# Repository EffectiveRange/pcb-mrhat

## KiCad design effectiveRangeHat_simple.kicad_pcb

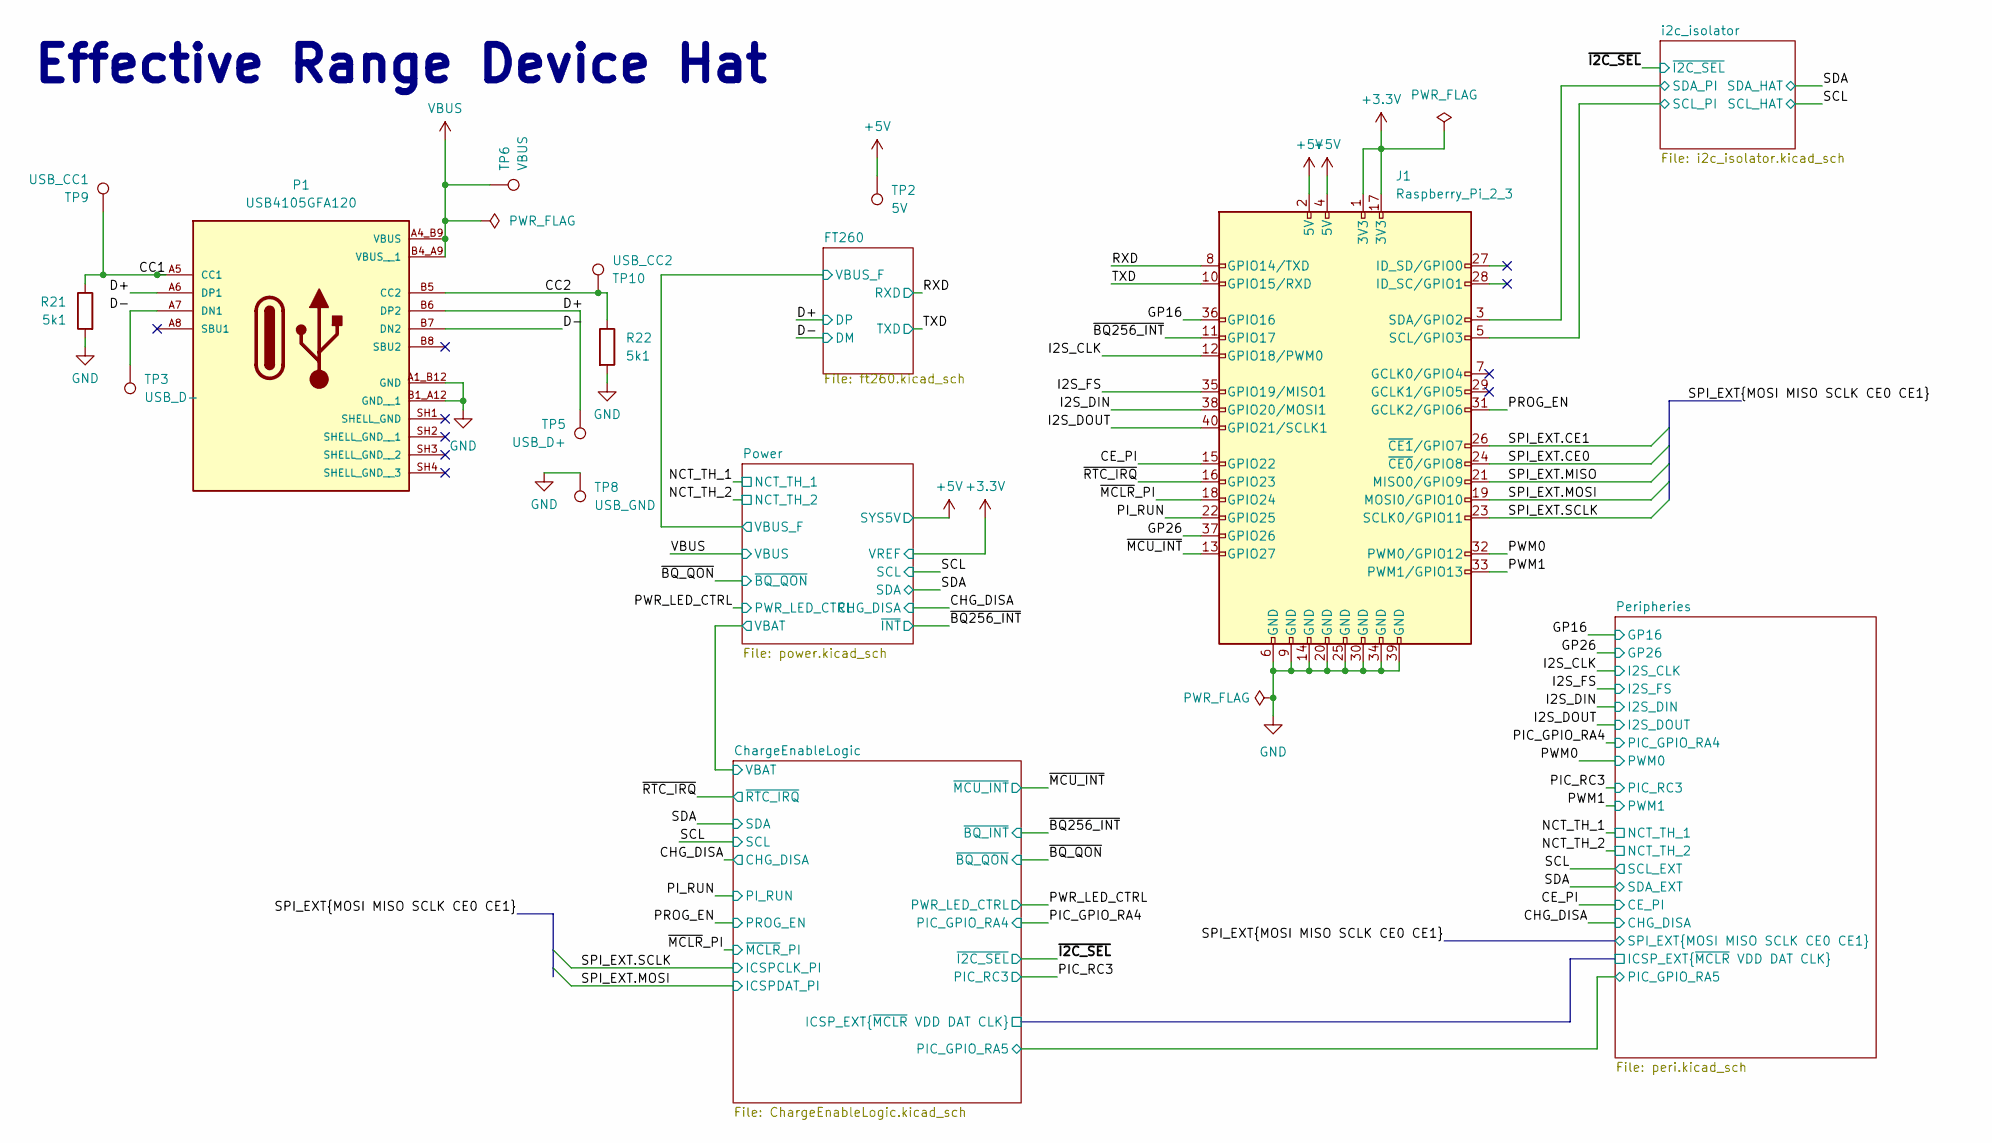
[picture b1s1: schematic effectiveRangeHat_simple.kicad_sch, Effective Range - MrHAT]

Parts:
J1: Raspberry_Pi_2_3; Raspberry_Pi_Zero_MountingHoles; MPN 61304021121
P1: USB4105GFA120; GCT_USB4105GFA120; PARTREV B3
R21, R22: 5k1; R_0402_1005Metric; MPN ERA-2AEB512X
TP2: 5V; TestPoint_Pad_D1.0mm
TP3: USB_D-; TestPoint_Pad_D1.0mm
TP5: USB_D+; TestPoint_Pad_D1.0mm
TP6: VBUS; TestPoint_Pad_D1.0mm
TP8: USB_GND; TestPoint_Pad_D1.0mm
TP9: USB_CC1; TestPoint_Pad_D1.0mm
TP10: USB_CC2; TestPoint_Pad_D1.0mm

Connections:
+3.3V: J1.1 (3V3), J1.17 (3V3); also elsewhere on the board
+5V: J1.2 (5V), J1.4 (5V), TP2.1; also elsewhere on the board
/CC1: P1.A5 (CC1), R21.1, TP9.1
/CC2: P1.B5 (CC2), R22.1, TP10.1
/CE_PI: J1.15 (GPIO22); also elsewhere on the board
/D+: P1.A6 (DP1), P1.B6 (DP2), TP5.1; also elsewhere on the board
/D-: P1.A7 (DN1), P1.B7 (DN2), TP3.1; also elsewhere on the board
/GP16: J1.36 (GPIO16); also elsewhere on the board
/GP26: J1.37 (GPIO26); also elsewhere on the board
/I2S_CLK: J1.12 (GPIO18/PWM0); also elsewhere on the board
/I2S_DIN: J1.38 (GPIO20/MOSI1); also elsewhere on the board
/I2S_DOUT: J1.40 (GPIO21/SCLK1); also elsewhere on the board
/I2S_FS: J1.35 (GPIO19/MISO1); also elsewhere on the board
/PI_RUN: J1.22 (GPIO25); also elsewhere on the board
/PROG_EN: J1.31 (GCLK2/GPIO6); also elsewhere on the board
/PWM0: J1.32 (PWM0/GPIO12); also elsewhere on the board
/PWM1: J1.33 (PWM1/GPIO13); also elsewhere on the board
/RXD: J1.8 (GPIO14/TXD); also elsewhere on the board
/SPI_EXT.CE0: J1.24 (~CE0/GPIO8); also elsewhere on the board
/SPI_EXT.CE1: J1.26 (~CE1/GPIO7); also elsewhere on the board
/SPI_EXT.MISO: J1.21 (MISO0/GPIO9); also elsewhere on the board
/SPI_EXT.MOSI: J1.19 (MOSI0/GPIO10); also elsewhere on the board
/SPI_EXT.SCLK: J1.23 (SCLK0/GPIO11); also elsewhere on the board
/TXD: J1.10 (GPIO15/RXD); also elsewhere on the board
/i2c_isolator/SCL_PI: J1.5 (SCL/GPIO3); also elsewhere on the board
/i2c_isolator/SDA_PI: J1.3 (SDA/GPIO2); also elsewhere on the board
/~BQ256_INT: J1.11 (GPIO17); also elsewhere on the board
/~MCLR_PI: J1.18 (GPIO24); also elsewhere on the board
/~MCU_INT: J1.13 (GPIO27); also elsewhere on the board
/~RTC_IRQ: J1.16 (GPIO23); also elsewhere on the board
GND: J1.6 (GND), J1.9 (GND), J1.14 (GND), J1.20 (GND), J1.25 (GND), J1.30 (GND), J1.34 (GND), J1.39 (GND), P1.A1_B12 (GND), P1.B1_A12 (GND__1), R21.2, R22.2, TP8.1; also elsewhere on the board
VBUS: P1.A4_B9 (VBUS), P1.B4_A9 (VBUS__1), TP6.1; also elsewhere on the board

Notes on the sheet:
Effective Range Device Hat

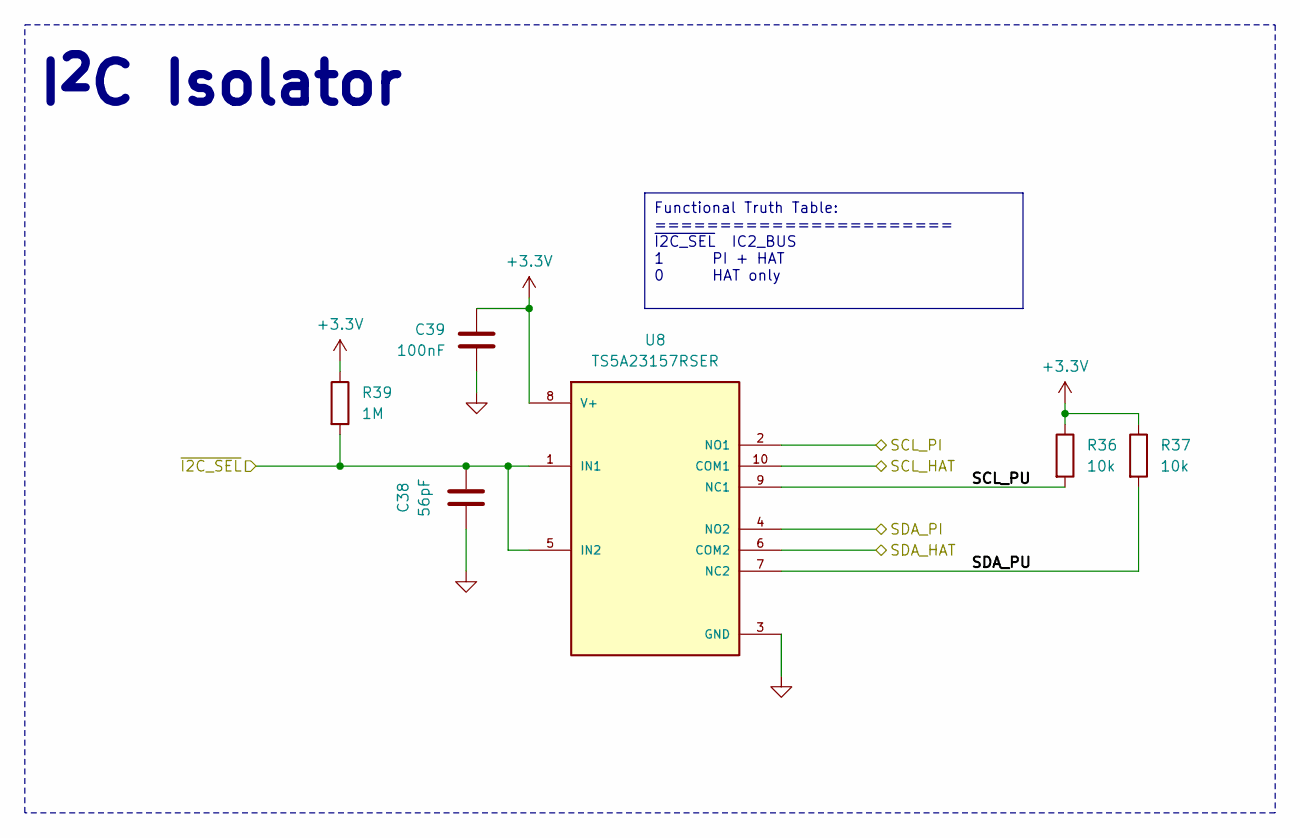
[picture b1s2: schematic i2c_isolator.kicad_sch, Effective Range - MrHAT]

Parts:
C38: 56pF; C_0402_1005Metric; MPN GRT1555C1H560JA02J
C39: 100nF; C_0402_1005Metric; MPN GRM155R71E104KE14J
R36, R37: 10k; R_0402_1005Metric; MPN ERJ-2GEJ103X
R39: 1M; R_0402_1005Metric; MPN ERJ-2RKF1004X
U8: TS5A23157RSER; IC_TS5A23157RSER; PARTREV 4220307/A 03/2020

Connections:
+3.3V: C39.2, R36.1, R37.1, R39.1, U8.8 (V+); also elsewhere on the board
/SCL: U8.10 (COM1); also elsewhere on the board
/SDA: U8.6 (COM2); also elsewhere on the board
/i2c_isolator/SCL_PI: U8.2 (NO1); also elsewhere on the board
/i2c_isolator/SCL_PU: R36.2, U8.9 (NC1)
/i2c_isolator/SDA_PI: U8.4 (NO2); also elsewhere on the board
/i2c_isolator/SDA_PU: R37.2, U8.7 (NC2)
/~I2C_SEL: C38.1, R39.2, U8.1 (IN1), U8.5 (IN2); also elsewhere on the board
GND: C38.2, C39.1, U8.3 (GND); also elsewhere on the board

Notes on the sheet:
Functional Truth Table: ======================= ~{I2C_SEL} IC2_BUS 1 PI + HAT 0 HAT only
I^{2}C Isolator

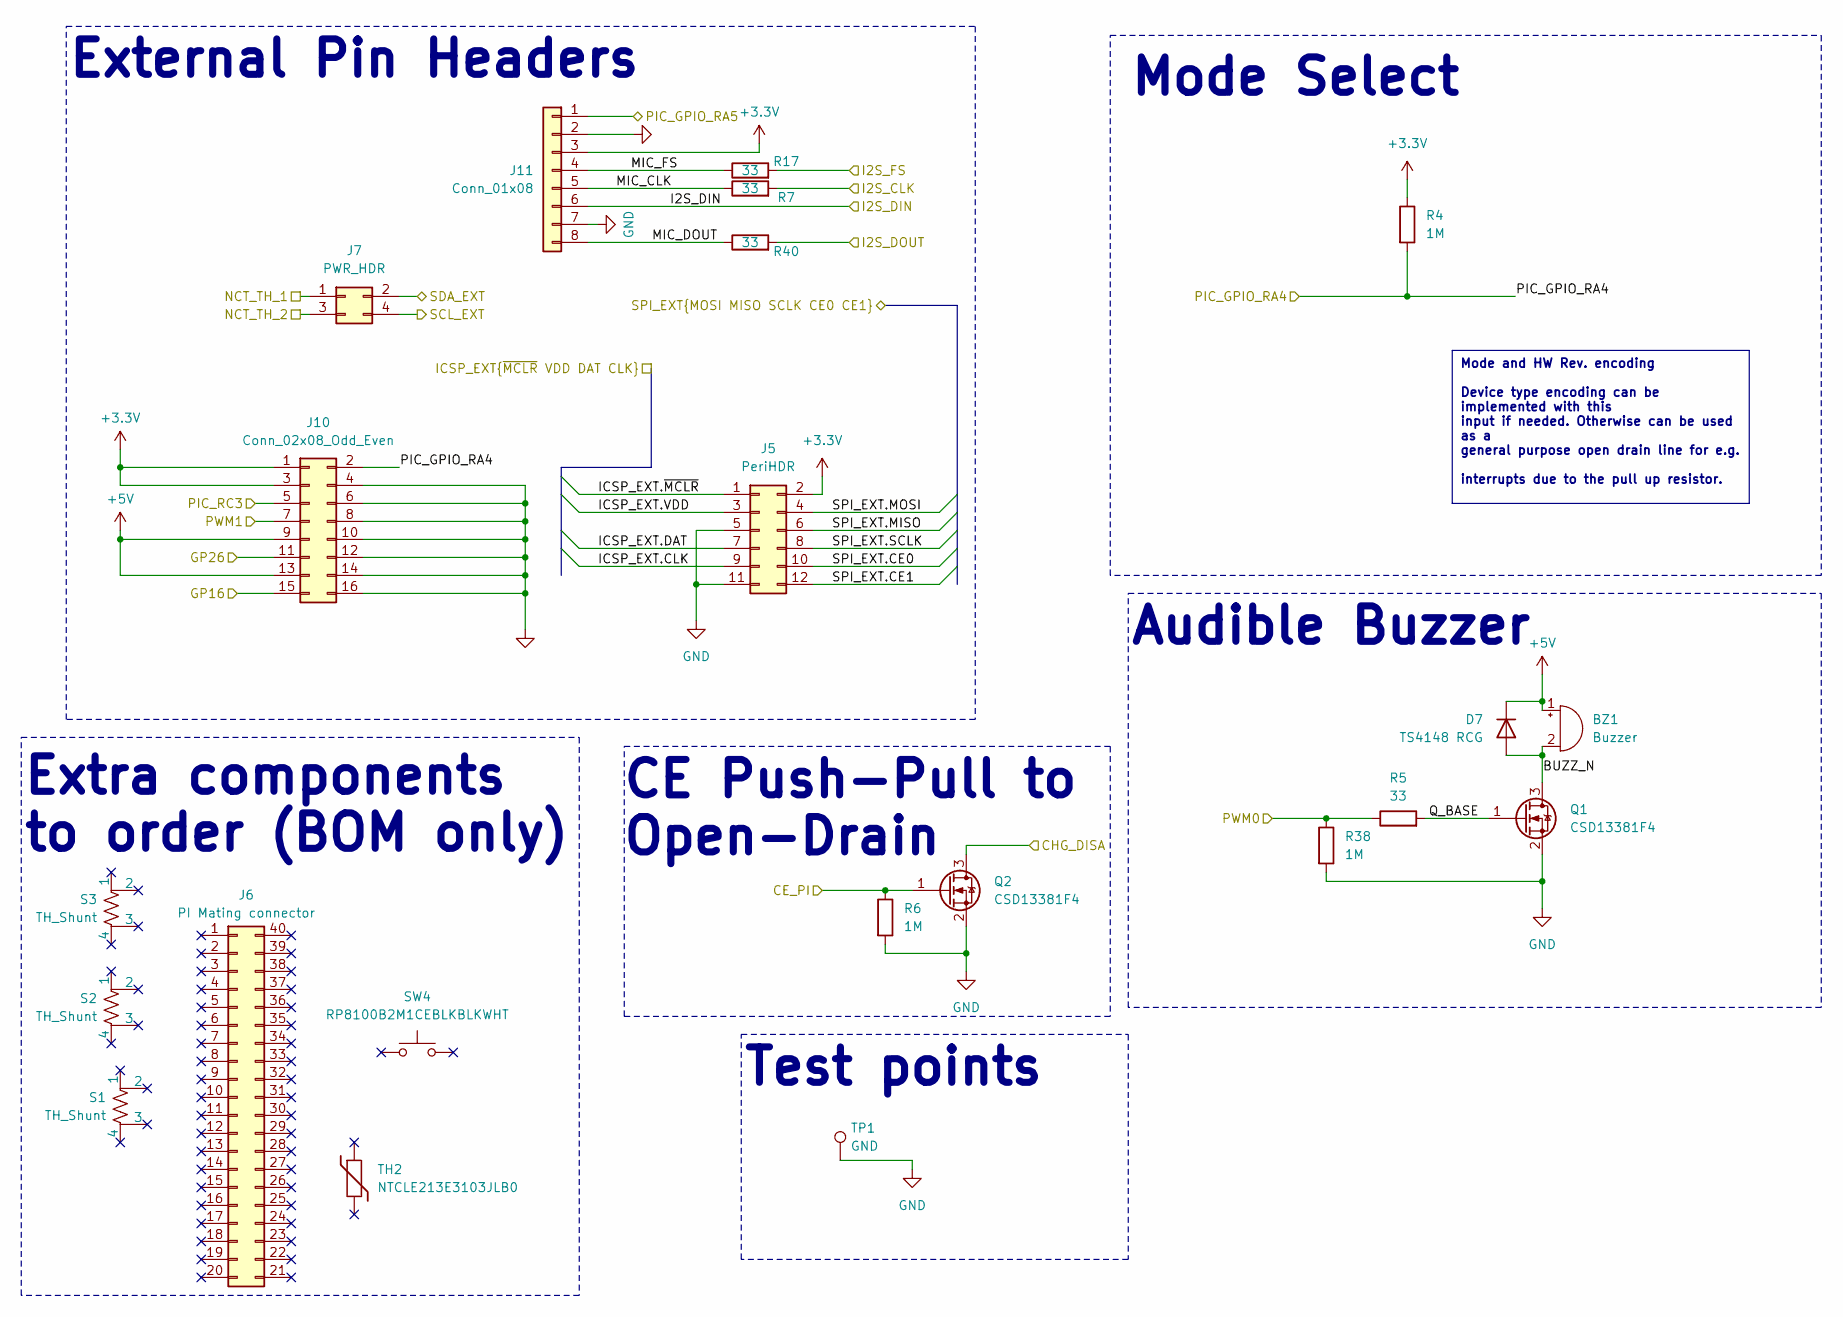
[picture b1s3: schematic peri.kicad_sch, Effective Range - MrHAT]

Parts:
BZ1: Buzzer; MagneticBuzzer_CUI_CMT-8504-100-SMT; MPN CMT-8504-100-SMT-TR
D7: TS4148 RCG; D_0603_1608Metric; MPN TS4148 RCG
J5: PeriHDR; PinHeader_2x06_P2.54mm_Vertical; MPN 61301221121
J6: PI Mating connector; MPN PPPC202LFBN-RC
J7: PWR_HDR; PinHeader_2x02_P2.54mm_Vertical; MPN 61300421121
J10: Conn_02x08_Odd_Even; PinHeader_2x08_P2.54mm_Vertical; MPN 61301621121
J11: Conn_01x08; PinHeader_1x08_P2.54mm_Vertical; MPN 61300811121
Q1, Q2: CSD13381F4; YJC0003A_TEX; MPN CSD13381F4
R4: 1M; R_0402_1005Metric; MPN ERJ-2RKF1004X
R5, R7, R17, R40: 33; R_0402_1005Metric; MPN ERJ-2RKF33R0X
R6, R38: 1M; R_0402_1005Metric; Tolerance 1%; MPN ERJ-2RKF1004X
S1, S2, S3: TH_Shunt; MPN QPC02SXGN-RC
SW4: RP8100B2M1CEBLKBLKWHT; MPN RP8100B2M1CEBLKBLKWHT
TH2: NTCLE213E3103JLB0; MPN NXFT15XH103FEAB035
TP1: GND; TestPoint_Pad_D1.0mm

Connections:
+3.3V: J5.2, J10.1, J10.3, J11.3, R4.1; also elsewhere on the board
+5V: BZ1.1 (+), D7.1 (K), J10.9, J10.13; also elsewhere on the board
/CE_PI: Q2.1 (G), R6.1; also elsewhere on the board
/CHG_DISA: Q2.3 (D); also elsewhere on the board
/ChargeEnableLogic/ICSP_EXT.CLK: J5.9; also elsewhere on the board
/ChargeEnableLogic/ICSP_EXT.DAT: J5.7; also elsewhere on the board
/ChargeEnableLogic/ICSP_EXT.VDD: J5.3; also elsewhere on the board
/ChargeEnableLogic/ICSP_EXT.~MCLR: J5.1; also elsewhere on the board
/ChargeEnableLogic/PIC_GPIO_RA5: J11.1; also elsewhere on the board
/GP16: J10.15; also elsewhere on the board
/GP26: J10.11; also elsewhere on the board
/I2S_CLK: R7.2; also elsewhere on the board
/I2S_DIN: J11.6; also elsewhere on the board
/I2S_DOUT: R40.2; also elsewhere on the board
/I2S_FS: R17.2; also elsewhere on the board
/NCT_TH_1: J7.1; also elsewhere on the board
/NCT_TH_2: J7.3; also elsewhere on the board
/PIC_GPIO_RA4: J10.2, R4.2; also elsewhere on the board
/PIC_RC3: J10.5; also elsewhere on the board
/PWM0: R5.1, R38.1; also elsewhere on the board
/PWM1: J10.7; also elsewhere on the board
/Peripheries/BUZZ_N: BZ1.2 (-), D7.2 (A), Q1.3 (D)
/Peripheries/MIC_CLK: J11.5, R7.1
/Peripheries/MIC_DOUT: J11.8, R40.1
/Peripheries/MIC_FS: J11.4, R17.1
/Peripheries/Q_BASE: Q1.1 (G), R5.2
/SCL: J7.4; also elsewhere on the board
/SDA: J7.2; also elsewhere on the board
/SPI_EXT.CE0: J5.10; also elsewhere on the board
/SPI_EXT.CE1: J5.12; also elsewhere on the board
/SPI_EXT.MISO: J5.6; also elsewhere on the board
/SPI_EXT.MOSI: J5.4; also elsewhere on the board
/SPI_EXT.SCLK: J5.8; also elsewhere on the board
GND: J5.5, J5.11, J10.4, J10.6, J10.8, J10.10, J10.12, J10.14, J10.16, J11.2, J11.7, Q1.2 (S), Q2.2 (S), R6.2, R38.2, TP1.1; also elsewhere on the board

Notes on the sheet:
Mode and HW Rev. encoding Device type encoding can be implemented with this input if needed. Otherwise can be used as a general purpose open drain line for e.g. interrupts due to the pull up resistor.
Mode Select
CE Push-Pull to Open-Drain
Audible Buzzer
Test points
Extra components to order (BOM only)
External Pin Headers

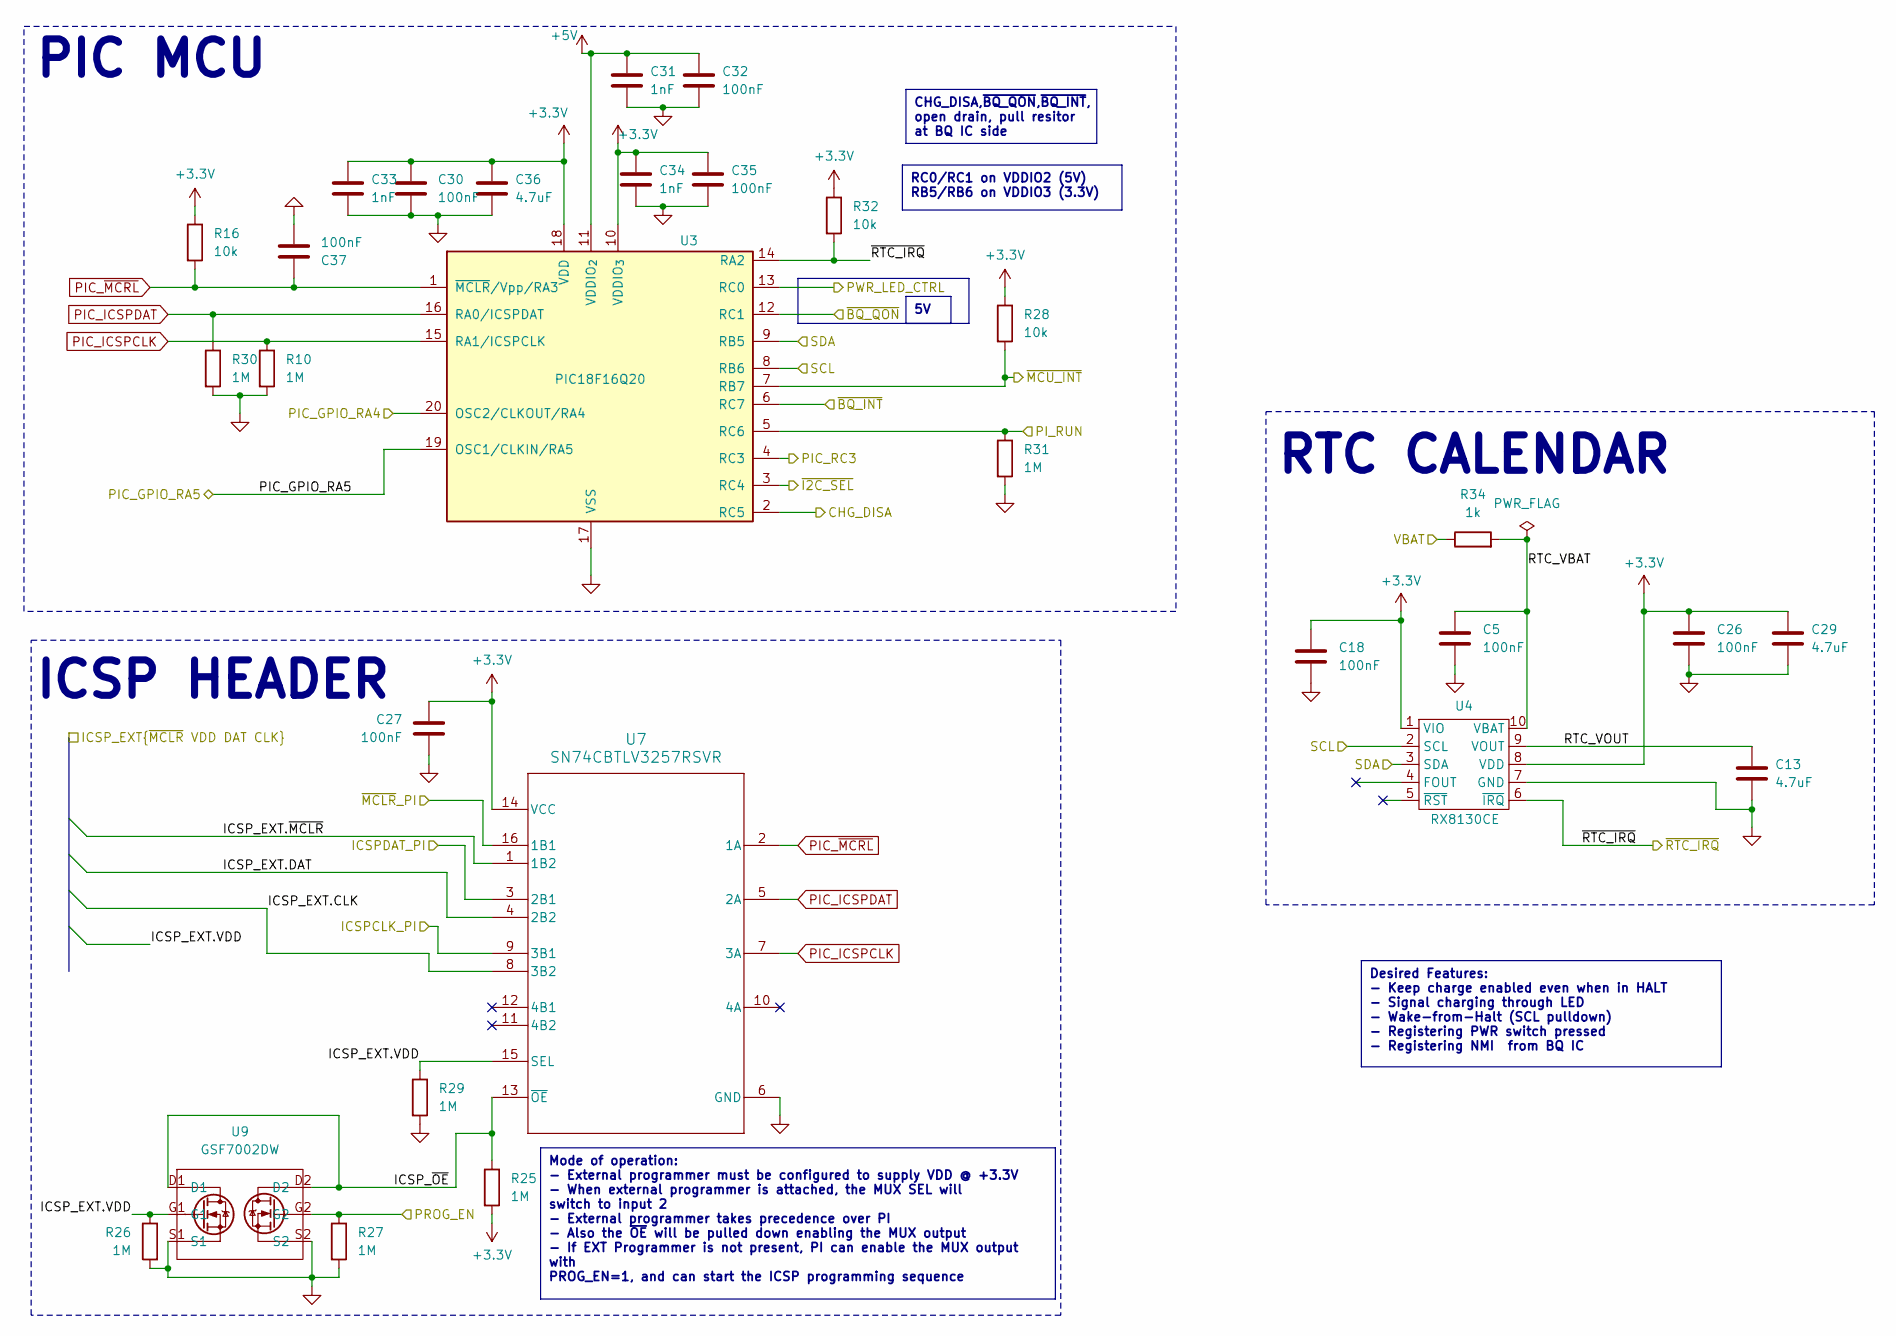
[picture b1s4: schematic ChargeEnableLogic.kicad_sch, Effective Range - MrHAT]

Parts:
C5, C18, C26, C27, C30, C32, C35, C37: 100nF; C_0402_1005Metric; MPN GRM155R71E104KE14J
C13, C29, C36: 4.7uF; C_0805_2012Metric; MPN GRM21BR61H475KE51L
C31, C33, C34: 1nF; C_0402_1005Metric; MPN GCM155R72A102KA37D
R10, R25, R29, R30, R31: 1M; R_0402_1005Metric; MPN ERJ-2RKF1004X
R16, R28, R32: 10k; R_0402_1005Metric; MPN ERJ-2GEJ103X
R26, R27: 1M; R_0402_1005Metric; Tolerance 1%; MPN ERJ-2RKF1004X
R34: 1k; R_0402_1005Metric; MPN ERJ-2RKF1001X
U3: PIC18F16Q20; VQFN-20-1EP_3x3mm_P0.4mm_EP1.7x1.7mm; MPN PIC18F16Q20-I/REB
U4: RX8130CE; MPN RX8130CE B0
U7: SN74CBTLV3257RSVR; RSV0016A; MPN SN74CBTLV3257RSVR
U9: GSF7002DW; MPN GSF7002DW

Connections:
+3.3V: C18.1, C26.1, C27.2, C29.1, C30.2, C33.1, C34.1, C35.1, C36.1, R16.1, R25.2, R28.1, R32.1, U3.10 (VDDIO_{3}), U3.18 (VDD), U4.1 (VIO), U4.8 (VDD), U7.14 (VCC); also elsewhere on the board
+5V: C31.1, C32.1, U3.11 (VDDIO_{2}); also elsewhere on the board
/CHG_DISA: U3.2 (RC5); also elsewhere on the board
/ChargeEnableLogic/ICSP_EXT.CLK: U7.8 (3B2); also elsewhere on the board
/ChargeEnableLogic/ICSP_EXT.DAT: U7.4 (2B2); also elsewhere on the board
/ChargeEnableLogic/ICSP_EXT.VDD: R26.1, R29.1, U7.15 (SEL), U9.G1; also elsewhere on the board
/ChargeEnableLogic/ICSP_EXT.~MCLR: U7.1 (1B2); also elsewhere on the board
/ChargeEnableLogic/ICSP_~OE: R25.1, U7.13 (~OE), U9.D1, U9.D2
/ChargeEnableLogic/PIC_GPIO_RA5: U3.19 (OSC1/CLKIN/RA5); also elsewhere on the board
/ChargeEnableLogic/RTC_VBAT: C5.1, R34.2, U4.10 (VBAT)
/ChargeEnableLogic/RTC_VOUT: C13.1, U4.9 (VOUT)
/PIC_GPIO_RA4: U3.20 (OSC2/CLKOUT/RA4); also elsewhere on the board
/PIC_RC3: U3.4 (RC3); also elsewhere on the board
/PI_RUN: R31.1, U3.5 (RC6); also elsewhere on the board
/PROG_EN: R27.1, U9.G2; also elsewhere on the board
/PWR_LED_CTRL: U3.13 (RC0); also elsewhere on the board
/Power/BAT: R34.1; also elsewhere on the board
/SCL: U3.8 (RB6), U4.2 (SCL); also elsewhere on the board
/SDA: U3.9 (RB5), U4.3 (SDA); also elsewhere on the board
/SPI_EXT.MOSI: U7.3 (2B1); also elsewhere on the board
/SPI_EXT.SCLK: U7.9 (3B1); also elsewhere on the board
/~BQ256_INT: U3.6 (RC7); also elsewhere on the board
/~BQ_QON: U3.12 (RC1); also elsewhere on the board
/~I2C_SEL: U3.3 (RC4); also elsewhere on the board
/~MCLR_PI: U7.16 (1B1); also elsewhere on the board
/~MCU_INT: R28.2, U3.7 (RB7); also elsewhere on the board
/~RTC_IRQ: R32.2, U3.14 (RA2), U4.6 (~IRQ); also elsewhere on the board
GND: C5.2, C13.2, C18.2, C26.2, C27.1, C29.2, C30.1, C31.2, C32.2, C33.2, C34.2, C35.2, C36.2, C37.1, R10.2, R26.2, R27.2, R29.2, R30.2, R31.2, U3.17 (VSS), U3.21 (VSS), U4.7 (GND), U7.6 (GND), U9.S1, U9.S2; also elsewhere on the board
PIC_ICSPCLK: R10.1, U3.15 (RA1/ICSPCLK), U7.7 (3A)
PIC_ICSPDAT: R30.1, U3.16 (RA0/ICSPDAT), U7.5 (2A)
PIC_~MCRL: C37.2, R16.2, U3.1 (~MCLR/Vpp/RA3), U7.2 (1A)

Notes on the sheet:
RC0/RC1 on VDDIO2 (5V) RB5/RB6 on VDDIO3 (3.3V)
Desired Features: - Keep charge enabled even when in HALT - Signal charging through LED - Wake-from-Halt (SCL pulldown) - Registering PWR switch pressed - Registering NMI from BQ IC
CHG_DISA,~{BQ_QON},~{BQ_INT}, open drain, pull resitor at BQ IC side
Mode of operation: - External programmer must be configured to supply VDD @ +3.3V - When external programmer is attached, the MUX SEL will switch to input 2 - External programmer takes precedence over PI - Also the ~{OE} will be pulled down enabling the MUX output - If EXT Programmer is not present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
RTC CALENDAR
ICSP HEADER
PIC MCU

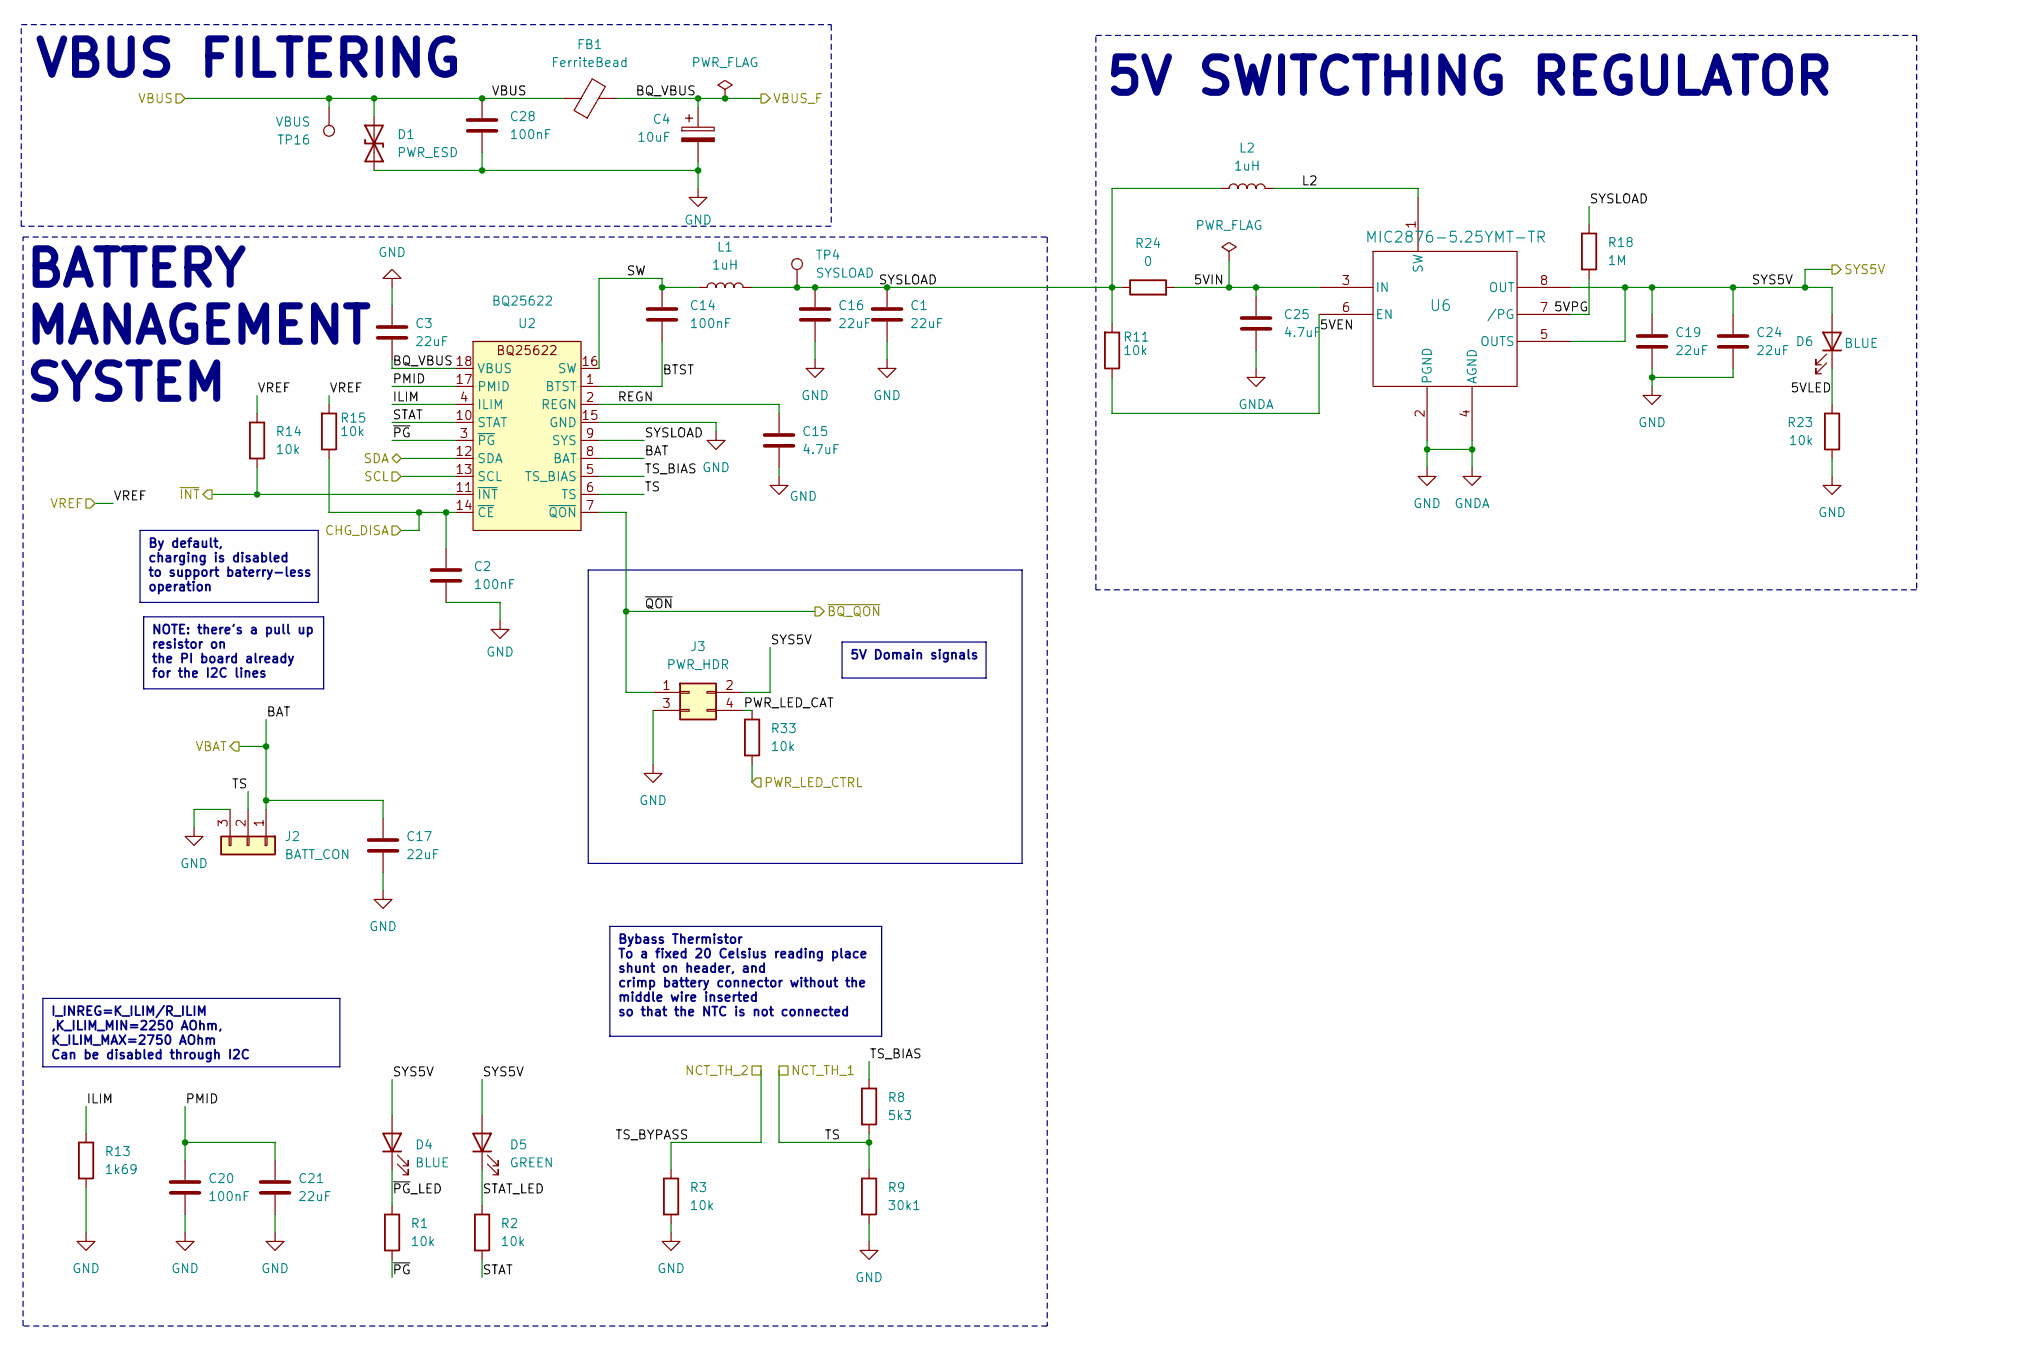
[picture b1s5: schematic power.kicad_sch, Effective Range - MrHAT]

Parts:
C1, C3, C16, C17, C19, C21, C24: 22uF; C_0805_2012Metric; MPN GRM21BR61E226ME44K
C2, C14, C20, C28: 100nF; C_0402_1005Metric; MPN GRM155R71E104KE14J
C4: 10uF; CAP_EEHZC1J100P; MPN EEH-ZC1J100P
C15, C25: 4.7uF; C_0805_2012Metric; MPN GRM21BR61H475KE51L
D1: PWR_ESD; D_0603_1608Metric; MPN PESD0603-240
D4, D6: BLUE; LED_0603; MPN 150060BS75000
D5: GREEN; LED_0603; MPN 150060GS75000
FB1: FerriteBead; L_1210_3225Metric; MPN BLE32PN260SH1L
J2: BATT_CON; JST_XH_B3B-XH-A_1x03_P2.50mm_Vertical; MPN B3B-XH-A
J3: PWR_HDR; PinHeader_2x02_P2.54mm_Vertical; MPN 61300421121
L1, L2: 1uH; L_1210_3225Metric; MPN DFE322520FD-1R0M=P2
R1, R2, R3, R11, R14, R15, R23, R33: 10k; R_0402_1005Metric; MPN ERJ-2GEJ103X
R8: 5k3; R_0402_1005Metric; MPN RT0402DRE075K3L
R9: 30k1; R_0402_1005Metric; MPN ERA-2AEB3012X
R13: 1k69; R_0402_1005Metric; MPN ERJ-2RKF1691X
R18: 1M; R_0402_1005Metric; Tolerance 1%; MPN ERJ-2RKF1004X
R24: 0; R_0603_1608Metric; Tolerance 1%; MPN ERJ-3GEY0R00V
TP4: SYSLOAD; TestPoint_Pad_D1.0mm
TP16: VBUS; TestPoint_Pad_D1.0mm
U2: BQ25622; MPN BQ25622RYKR
U6: MIC2876-5.25YMT-TR; TDFN22-8LD-PL-1_MCH; MPN MIC2876-5.25YMT-TR

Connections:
+3.3V: R14.1, R15.2; also elsewhere on the board
+5V: C19.1, C24.1, D4.2 (A), D5.2 (A), D6.2 (A), J3.2, U6.5 (OUTS), U6.8 (OUT); also elsewhere on the board
/CHG_DISA: C2.1, R15.1, U2.14 (~CE); also elsewhere on the board
/FT260/VCCIN: C3.2, C4.1, FB1.2, U2.18 (VBUS); also elsewhere on the board
/NCT_TH_1: J2.2, R8.2, R9.1, U2.6 (TS); also elsewhere on the board
/NCT_TH_2: R3.1; also elsewhere on the board
/PWR_LED_CTRL: R33.2; also elsewhere on the board
/Power/5VEN: R11.1, U6.6 (EN)
/Power/5VIN: C25.1, R24.2, U6.3 (IN)
/Power/5VLED: D6.1 (K), R23.1
/Power/5VPG: R18.2, U6.7 (/PG)
/Power/BAT: C17.1, J2.1, U2.8 (BAT); also elsewhere on the board
/Power/BTST: C14.2, U2.1 (BTST)
/Power/ILIM: R13.1, U2.4 (ILIM)
/Power/L2: L2.2, U6.1 (SW)
/Power/PMID: C20.1, C21.1, U2.17 (PMID)
/Power/PWR_LED_CAT: J3.4, R33.1
/Power/REGN: C15.1, U2.2 (REGN)
/Power/STAT: R2.2, U2.10 (STAT)
/Power/STAT_LED: D5.1 (K), R2.1
/Power/SW: C14.1, L1.1, U2.16 (SW)
/Power/SYSLOAD: C1.1, C16.1, L1.2, L2.1, R11.2, R18.1, R24.1, TP4.1, U2.9 (SYS)
/Power/TS_BIAS: R8.1, U2.5 (TS_BIAS)
/Power/~PG: R1.2, U2.3 (~PG)
/Power/~PG_LED: D4.1 (K), R1.1
/SCL: U2.13 (SCL); also elsewhere on the board
/SDA: U2.12 (SDA); also elsewhere on the board
/~BQ256_INT: R14.2, U2.11 (~INT); also elsewhere on the board
/~BQ_QON: J3.1, U2.7 (~QON); also elsewhere on the board
GND: C1.2, C2.2, C3.1, C4.2, C15.2, C16.2, C17.2, C19.2, C20.2, C21.2, C24.2, C25.2, C28.2, D1.1 (A1), J2.3, J3.3, R3.2, R9.2, R13.2, R23.2, U2.15 (GND), U6.2 (PGND), U6.4 (AGND), U6.9 (AGND); also elsewhere on the board
VBUS: C28.1, D1.2 (A2), FB1.1, TP16.1; also elsewhere on the board

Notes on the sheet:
NOTE: there's a pull up resistor on the PI board already for the I2C lines
Bybass Thermistor To a fixed 20 Celsius reading place shunt on header, and crimp battery connector without the middle wire inserted so that the NTC is not connected
I_INREG=K_ILIM/R_ILIM ,K_ILIM_MIN=2250 AOhm, K_ILIM_MAX=2750 AOhm Can be disabled through I2C
5V Domain signals
By default, charging is disabled to support baterry-less operation
5V SWITCTHING REGULATOR
BATTERY MANAGEMENT SYSTEM
VBUS FILTERING

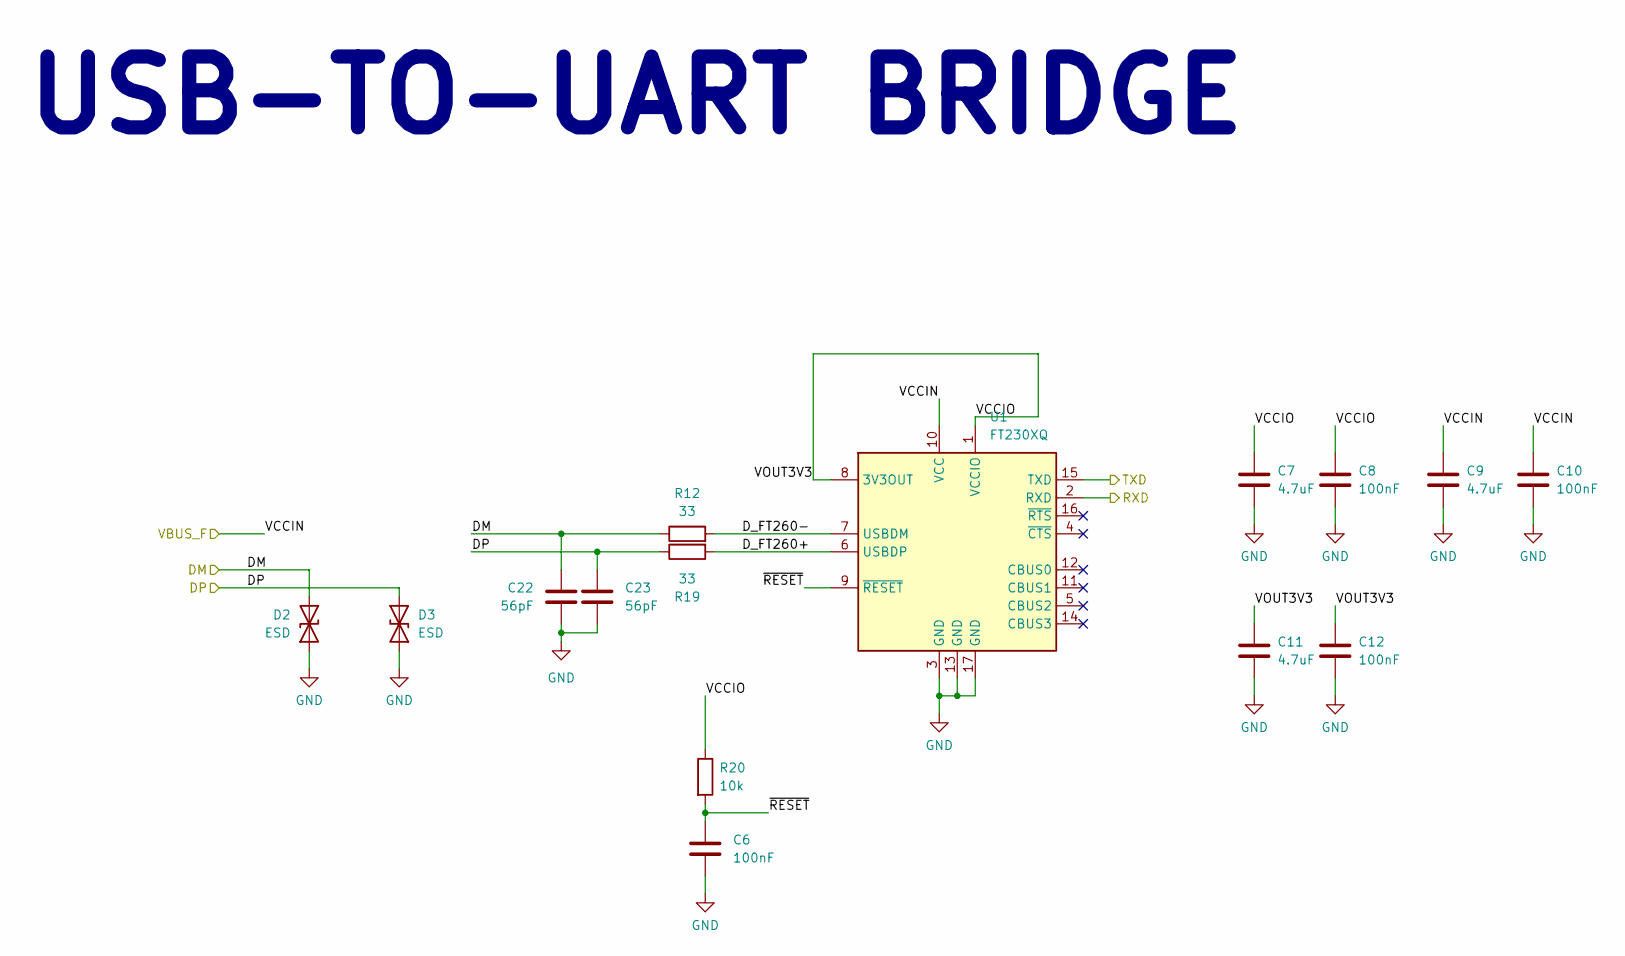
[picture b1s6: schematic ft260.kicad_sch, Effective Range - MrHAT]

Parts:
C6, C8, C10, C12: 100nF; C_0402_1005Metric; MPN GRM155R71E104KE14J
C7, C9, C11: 4.7uF; C_0805_2012Metric; MPN GRM21BR61H475KE51L
C22, C23: 56pF; C_0402_1005Metric; MPN GRT1555C1H560JA02J
D2, D3: ESD; D_0402_1005Metric; MPN ESDUD05BFX
R12, R19: 33; R_0402_1005Metric; MPN ERJ-2RKF33R0X
R20: 10k; R_0402_1005Metric; MPN ERJ-2GEJ103X
U1: FT230XQ; QFN-16-1EP_4x4mm_P0.65mm_EP2.1x2.1mm_4ThermalVias; MPN FT230XQ-T

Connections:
/D+: C23.1, D3.2 (A2), R19.1; also elsewhere on the board
/D-: C22.1, D2.2 (A2), R12.1; also elsewhere on the board
/FT260/D_FT260+: R19.2, U1.6 (USBDP)
/FT260/D_FT260-: R12.2, U1.7 (USBDM)
/FT260/VCCIN: C9.1, C10.1, U1.10 (VCC); also elsewhere on the board
/FT260/VCCIO: C7.1, C8.1, C11.1, C12.1, R20.1, U1.1 (VCCIO), U1.8 (3V3OUT)
/FT260/~RESET: C6.1, R20.2, U1.9 (~RESET)
/RXD: U1.2 (RXD); also elsewhere on the board
/TXD: U1.15 (TXD); also elsewhere on the board
GND: C6.2, C7.2, C8.2, C9.2, C10.2, C11.2, C12.2, C22.2, C23.2, D2.1 (A1), D3.1 (A1), U1.3 (GND), U1.13 (GND), U1.17 (GND); also elsewhere on the board

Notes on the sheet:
USB-TO-UART BRIDGE

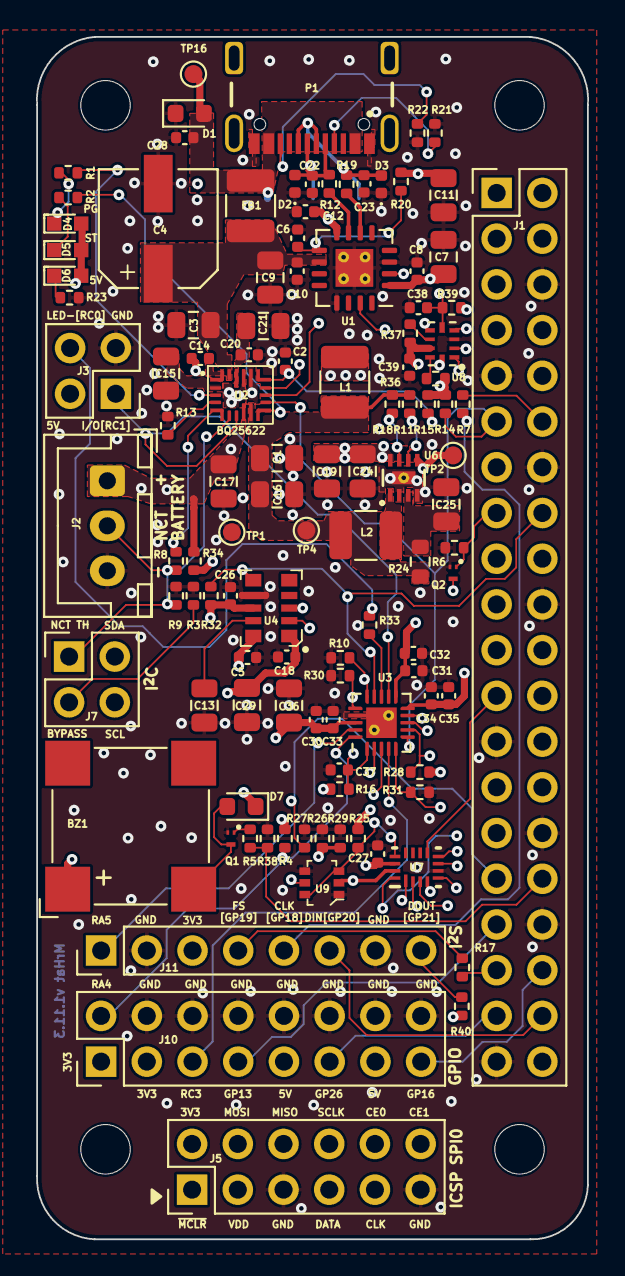
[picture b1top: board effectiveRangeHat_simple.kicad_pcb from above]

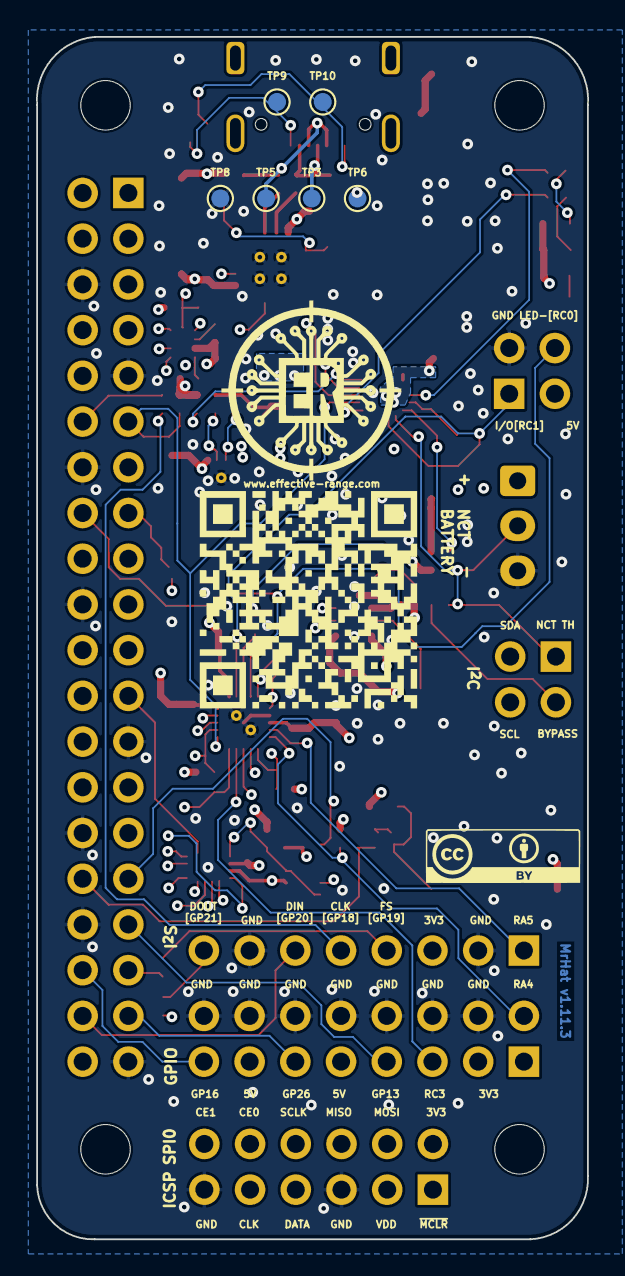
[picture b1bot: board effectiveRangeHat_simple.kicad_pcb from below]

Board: 8 copper layers, 30.6 x 66.8 mm, 117 parts (6 on the bottom side), 83 nets.

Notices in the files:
ChargeEnableLogic.kicad_sch:
visit https://creativecommons.org/licenses/by/4.0
is licensed under CC BY 4.0. To view a copy of this license,
License: MrHAT © 2024 by Ferenc Nandor Janky & Attila Gombos
